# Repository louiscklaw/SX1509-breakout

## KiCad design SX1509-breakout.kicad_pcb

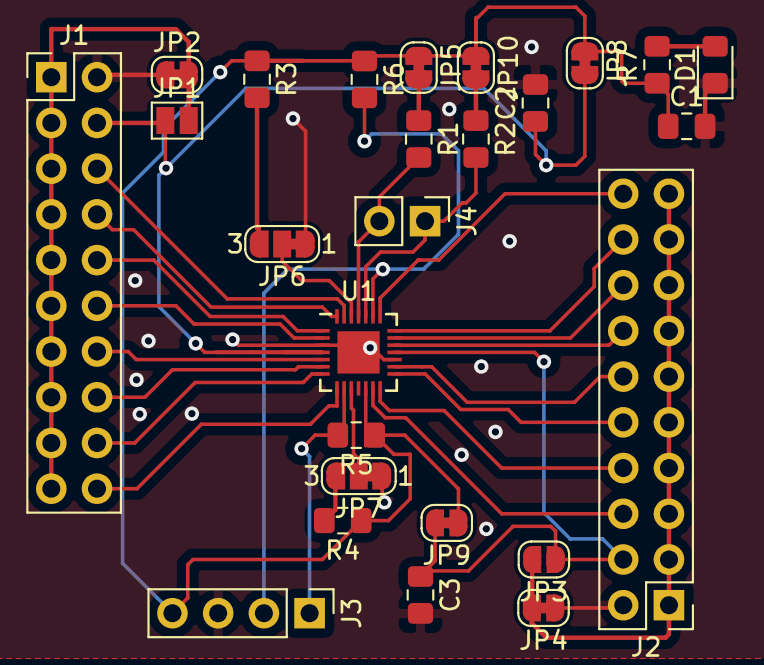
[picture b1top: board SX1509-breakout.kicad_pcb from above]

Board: 2 copper layers, 26 parts (0 on the bottom side), 33 nets.

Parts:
C1, C2, C3: 106; C_0805_2012Metric_Pad1.15x1.40mm_HandSolder
D1: LED; LED_0805_2012Metric_Pad1.15x1.40mm_HandSolder
J1: IO0_TO_IO7; PinHeader_2x10_P2.54mm_Vertical
J2: IO8_TO_IO15; PinHeader_2x10_P2.54mm_Vertical
J3: Conn_01x06; PinHeader_1x04_P2.54mm_Vertical
J4: Conn_01x06; PinHeader_1x02_P2.54mm_Vertical
JP1: B-VCC1; SolderJumper-2_P1.3mm_Open_Pad1.0x1.5mm
JP2, JP4: SolderJumper_2_Bridged; SolderJumper-2_P1.3mm_Bridged_RoundedPad1.0x1.5mm
JP3: B-VCC2; SolderJumper-2_P1.3mm_Open_RoundedPad1.0x1.5mm
JP5: SCL_EN; SolderJumper-2_P1.3mm_Bridged_RoundedPad1.0x1.5mm
JP6: ADDR1_EN; SolderJumper-3_P1.3mm_Bridged12_RoundedPad1.0x1.5mm_NumberL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
JP7: ADDR0_EN; SolderJumper-3_P1.3mm_Bridged12_RoundedPad1.0x1.5mm_NumberL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
JP8: VCC1-3.3V; SolderJumper-2_P1.3mm_Bridged_RoundedPad1.0x1.5mm
JP9: VCC2-3.3V; SolderJumper-2_P1.3mm_Bridged_RoundedPad1.0x1.5mm
JP10: SDA_EN; SolderJumper-2_P1.3mm_Bridged_RoundedPad1.0x1.5mm
R1, R2, R3, R4, R5, R6: 103; R_0805_2012Metric_Pad1.15x1.40mm_HandSolder
R7: 102; R_0805_2012Metric_Pad1.15x1.40mm_HandSolder
U1: SX1509; UQFN-28-1EP_4x4mm_P0.4mm_EP2.35x2.35mm

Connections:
+3V3: C1.1, J3.4, JP5.1, JP8.1, JP9.1, JP10.1, R3.1, R4.1, R5.1, R6.1, R7.1, U1.12
/ADDR0: JP6.2, U1.26
/ADDR1: JP7.2, U1.10
/IO0: J1.6, U1.27
/IO1: J1.8, U1.28
/IO2: J1.10, U1.1
/IO3: J1.12, U1.2
/IO4: J1.14, U1.5
/IO5: J1.16, U1.6
/IO6: J1.18, U1.7
/IO7: J1.20, U1.8
/IO8: J2.6, U1.13
/IO9: J2.8, U1.14
/IO10: J2.10, U1.15
/IO11: J2.12, U1.16
/IO12: J2.14, U1.19
/IO13: J2.16, U1.20
/IO14: J2.18, U1.21
/IO15: J2.20, U1.22
/NINT: J3.1, R5.2, U1.9
/NRESET: J3.2, R6.2, U1.23
/SCL: J4.2, R1.2, U1.25
/SDA: J4.1, R2.2, U1.24
/VCC1: C2.1, J1.4, JP1.1, JP8.2, U1.4
/VCC2: C3.1, J2.4, JP3.1, JP9.2, U1.18
GND: C1.2, C2.2, C3.2, D1.1, J1.2, J2.2, J3.3, JP2.1, JP4.1, JP6.1, JP7.1, U1.3, U1.17, U1.29
unnamed: D1.2, R7.2
unnamed: J1.1, J1.3, J1.5, J1.7, J1.9, J1.11, J1.13, J1.15, J1.17, J1.19, JP1.2, JP2.2
unnamed: J2.1, J2.3, J2.5, J2.7, J2.9, J2.11, J2.13, J2.15, J2.17, J2.19, JP3.2, JP4.2
unnamed: JP5.2, R1.1
unnamed: JP6.3, R3.2
unnamed: JP7.3, R4.2
unnamed: JP10.2, R2.1

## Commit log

2018-10-12 init commit,.
2020-05-07 ci: init travis token,
2020-05-07 ci: init travis build config,
